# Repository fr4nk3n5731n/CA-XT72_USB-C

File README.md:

# CA-XT72-USB-C 
This project is a Midland CA-XT72 compatible USB-C replacement board.

The CA-XT72 is a USB powered charging cradle that ships with a USB Micro B board.

It's being sold alongside a couple of Midland Walkie Talkies like the [Midland XT70](https://www.midlandeurope.com/en_150/products/xt70) for example.

# Components
Recommended board thickness: __1mm__

| Id | Designator | Footprint | Quantity | Designation           | Supplier and ref                                                                                                                                                      |
| -- | ---------- | --------- | -------- |-----------------------|-----------------------------------------------------------------------------------------------------------------------------------------------------------------------|
| 1 | J1 | UJC-HP-3-SMT-TR | 1 | UJC-HP-3-SMT-TR:CUI_UJC-HP-3-SMT-TR      | [Mouser](https://eu.mouser.com/ProductDetail/CUI-Devices/UJC-HP-3-SMT-TR), [DigiKey](https://www.digikey.com/en/products/detail/cui-devices/UJC-HP-3-SMT-TR/12173295) |
| 2 | F1 | 500mA | 1 | C1F 500:FUSC3215X83N | [Mouser](https://eu.mouser.com/ProductDetail/Bel-Fuse/C1F-500), [DigiKey](https://www.digikey.com/en/products/detail/bel-fuse-inc/c1f-500/4968258)                    |
| 3 | R1,R2 | R_0402_1005Metric_Pad0.72x0.64mm_HandSolder | 2 | 0402 5.1k             | [Mouser](https://eu.mouser.com/ProductDetail/TE-Connectivity-Holsworthy/CRG0402F5K1), [DigiKey](https://www.digikey.com/en/products/detail/te-connectivity-passive-product/CRG0402F5K1/2390558)                                                                     |

# Extra Footprint Sources:
- USB-C Port: https://www.snapeda.com/parts/UJC-HP-3-SMT-TR/CUI%20Devices/view-part
- Fuse: https://www.snapeda.com/parts/C1F-500/Bel%20Fuse/view-part

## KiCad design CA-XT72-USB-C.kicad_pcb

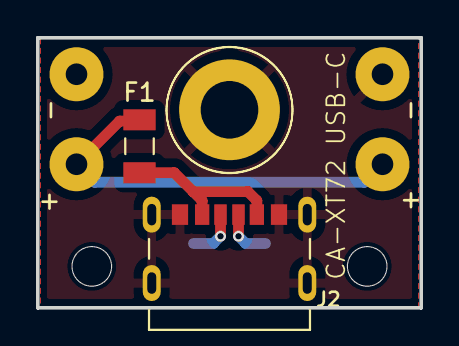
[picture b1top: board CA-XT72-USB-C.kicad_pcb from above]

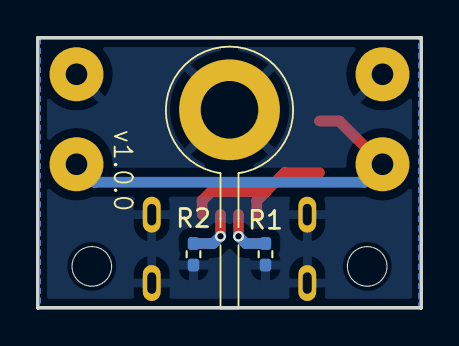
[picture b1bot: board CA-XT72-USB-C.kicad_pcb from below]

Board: 2 copper layers, 21.3 x 15.0 mm, 8 parts (2 on the bottom side), 5 nets.

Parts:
+: MountingHole_Pad; MountingHole_2.2mm_M2_DIN965_Pad
+#2: MountingHole_Pad; MountingHole_2.2mm_M2_DIN965_Pad
-: MountingHole_Pad; MountingHole_2.2mm_M2_DIN965_Pad
-#2: MountingHole_Pad; MountingHole_2.2mm_M2_DIN965_Pad
F1: 500mA; FUSC3215X83N
J2: UJC-HP-3-SMT-TR; CUI_UJC-HP-3-SMT-TR
R1, R2: 5.1k; R_0402_1005Metric_Pad0.72x0.64mm_HandSolder

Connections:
5V: +.1, +#2.1, F1.2
CC1: J2.A5 (CC1), R1.1
CC2: J2.B5 (CC2), R2.1
GND: -.1, -#2.1, J2.A12 (GND), J2.B12 (GND), J2.S1 (SHIELD), J2.S2 (SHIELD), J2.S3 (SHIELD), J2.S4 (SHIELD), R1.2, R2.2
VCC: F1.1, J2.A9 (V-BUS), J2.B9 (V-BUS)

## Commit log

2024-06-22 initial upload
